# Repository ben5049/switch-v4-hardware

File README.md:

# Switch v4 Hardware

KiCad design files for the 4th iteration of my single pair Ethernet (SPE) switch. The firmware can be found in [unified-switch-firmware](https://github.com/ben5049/unified-switch-firmware).

Also see my post on [r/embedded](https://www.reddit.com/r/embedded/comments/1mxale6/i_built_a_single_pair_ethernet_switch/)!

## Design

See the [schematic](docs/schematics/switch-main-v4.pdf) for a block diagram and in-depth details.

The main switch chip is an [SJA1105QEL](https://www.nxp.com/products/SJA1105PQRS) from NXP. It is configured via SPI by an [STM32H573IIK3Q](https://www.st.com/resource/en/datasheet/stm32h573ai.pdf). The STM32 is also connected by reduced media independent interface (RMII) to the switch so it is able to send and receive management traffic such as Spanning Tree Protocol ([STP](https://en.wikipedia.org/wiki/Spanning_Tree_Protocol)) BPDUs as well as Precision Time Protocol (PTP) packets and diagnostic information.

The connections for each SJA1105 port are shown below:

| Port | Speed (Mbps) | Description                                            |
| ---- | ------------ | ------------------------------------------------------ |
| 0    | 100/1000     | Marvell 88Q2112 100/1000BASE-T1 Ethernet PHY           |
| 1    | 100/1000     | Marvell 88Q2112 100/1000BASE-T1 Ethernet PHY with PoDL |
| 2    | 100/1000     | Marvell 88Q2112 100/1000BASE-T1 Ethernet PHY with PoDL |
| 3    | 10           | Microchip LAN8671 10BASE-T1S Ethernet PHY with PoDL    |
| 4    | 100          | Internal STM32 management processor                    |

### PoDL PSE

Power over Datalines ([PoDL](https://en.wikipedia.org/wiki/Power_over_Ethernet#PoDL)) is similar to Power over Ethernet ([PoE](https://en.wikipedia.org/wiki/Power_over_Ethernet)) but for SPE. In regular PoE power is sent over the center taps of the transformers, however in SPE there is only one (or no) transformer so this wouldn't work. Instead, DC power is injected into the datalines in the Coupling Decoupling Network (CDN) using differential mode inductors (DMI). The switch is only capable of being a Power Sourcing Equipment (PSE) which powers other devices. It must get its own power through the other connectors on the board.

PoDL has been implemented on ports 1, 2 and 3 of the switch.

- Ports 1 and 2 are able to output 1.1A each and use a simple detection method before supplying power to a load. Firstly ~14mA is sent down the cable, then if the bus voltage is between 4.05 and 4.55V then the full supply is enabled (typically 24V). This is usually done by a zener diode on the other end of the cable.

- Port 3 is also able to output 1.1A and uses a custom multidrop PoDL implementation. Detection is done by powering the bus at 6.5V, then each device on the bus draws 1mA for every 1W of power they want. Then the full supply is enabled.

An [STM32H503KBU6](https://www.st.com/resource/en/datasheet/stm32h503eb.pdf) is used as a secondary processor to control the PoDL operations. It talks to the primary processor via UART through an optocoupler. This means the data and power circuits are galvanically isolated.

## Test Rig

The [test rig PCB](pcbs/switch-main-v4-test-rig) is designed so that its pogo pins align directly with the test pads on the bottom of the main switch board. This means a debugger can be connected without needing to include a header on the main board.

## Versions

| Version | Description |
| ------- | ----------- |
| v4.1.1  | Updated to Kicad v10 |
| v4.1.0  | Fixed bugs from first revision |
| v4.0.0  | First release |

See the [errata](docs/errata.md) for details on bugs.

## References

Datasheets:
- [88Q2112 Datasheet](https://www.infineon.com/assets/row/public/documents/10/49/infineon-brightlane-88q2110-88q2112-datasheet-datasheet-en.pdf) (requires an Infineon account)
- [SJA1105 Datasheet](https://www.nxp.com/docs/en/data-sheet/SJA1105PQRS.pdf)
- [LAN8671 Datasheet](https://ww1.microchip.com/downloads/aemDocuments/documents/AIS/ProductDocuments/DataSheets/LAN8670-1-2-Data-Sheet-60001573.pdf)

PoDL:
- [How to Implement an IEEE 802.3cg or 802.3bu-Compliant PoDL PSE](https://www.ti.com/lit/ab/snla395/snla395.pdf?ts=1745823061950) - TI
- [1000BASE-T1 PoDL Reference design](https://www.ti.com/lit/ug/tiduf49/tiduf49.pdf?ts=1746159399261&ref_url=https%253A%252F%252Fwww.google.com%252F) - TI
- [PSE Schematic](https://www.ti.com/lit/df/tidmco4/tidmco4.pdf?ts=1746307249429) - TI
- [IEEE 802.3cg 10BASE-T1L Power over Data Lines Powered Device Design](https://www.ti.com/lit/an/snvaa25a/snvaa25a.pdf?ts=1745871367852) - TI
    - References non-existent inductors :/
- [SINGLE PAIR ETHERNET FILTER DESIGN](https://www.we-online.com/files/pdf1/single_pair_ethernet.pdf) - WE
- [Power Injection Inductors for 10BASE-T1 PoDL](https://www.coilcraft.com/en-us/applications/power-injection-inductors-for-10base-t1-podl/) - Coilcraft
- [10BASE-T1L Converter w/ PoE+PoDL](https://matthewtran.dev/2024/08/10base-t1l-converter/)

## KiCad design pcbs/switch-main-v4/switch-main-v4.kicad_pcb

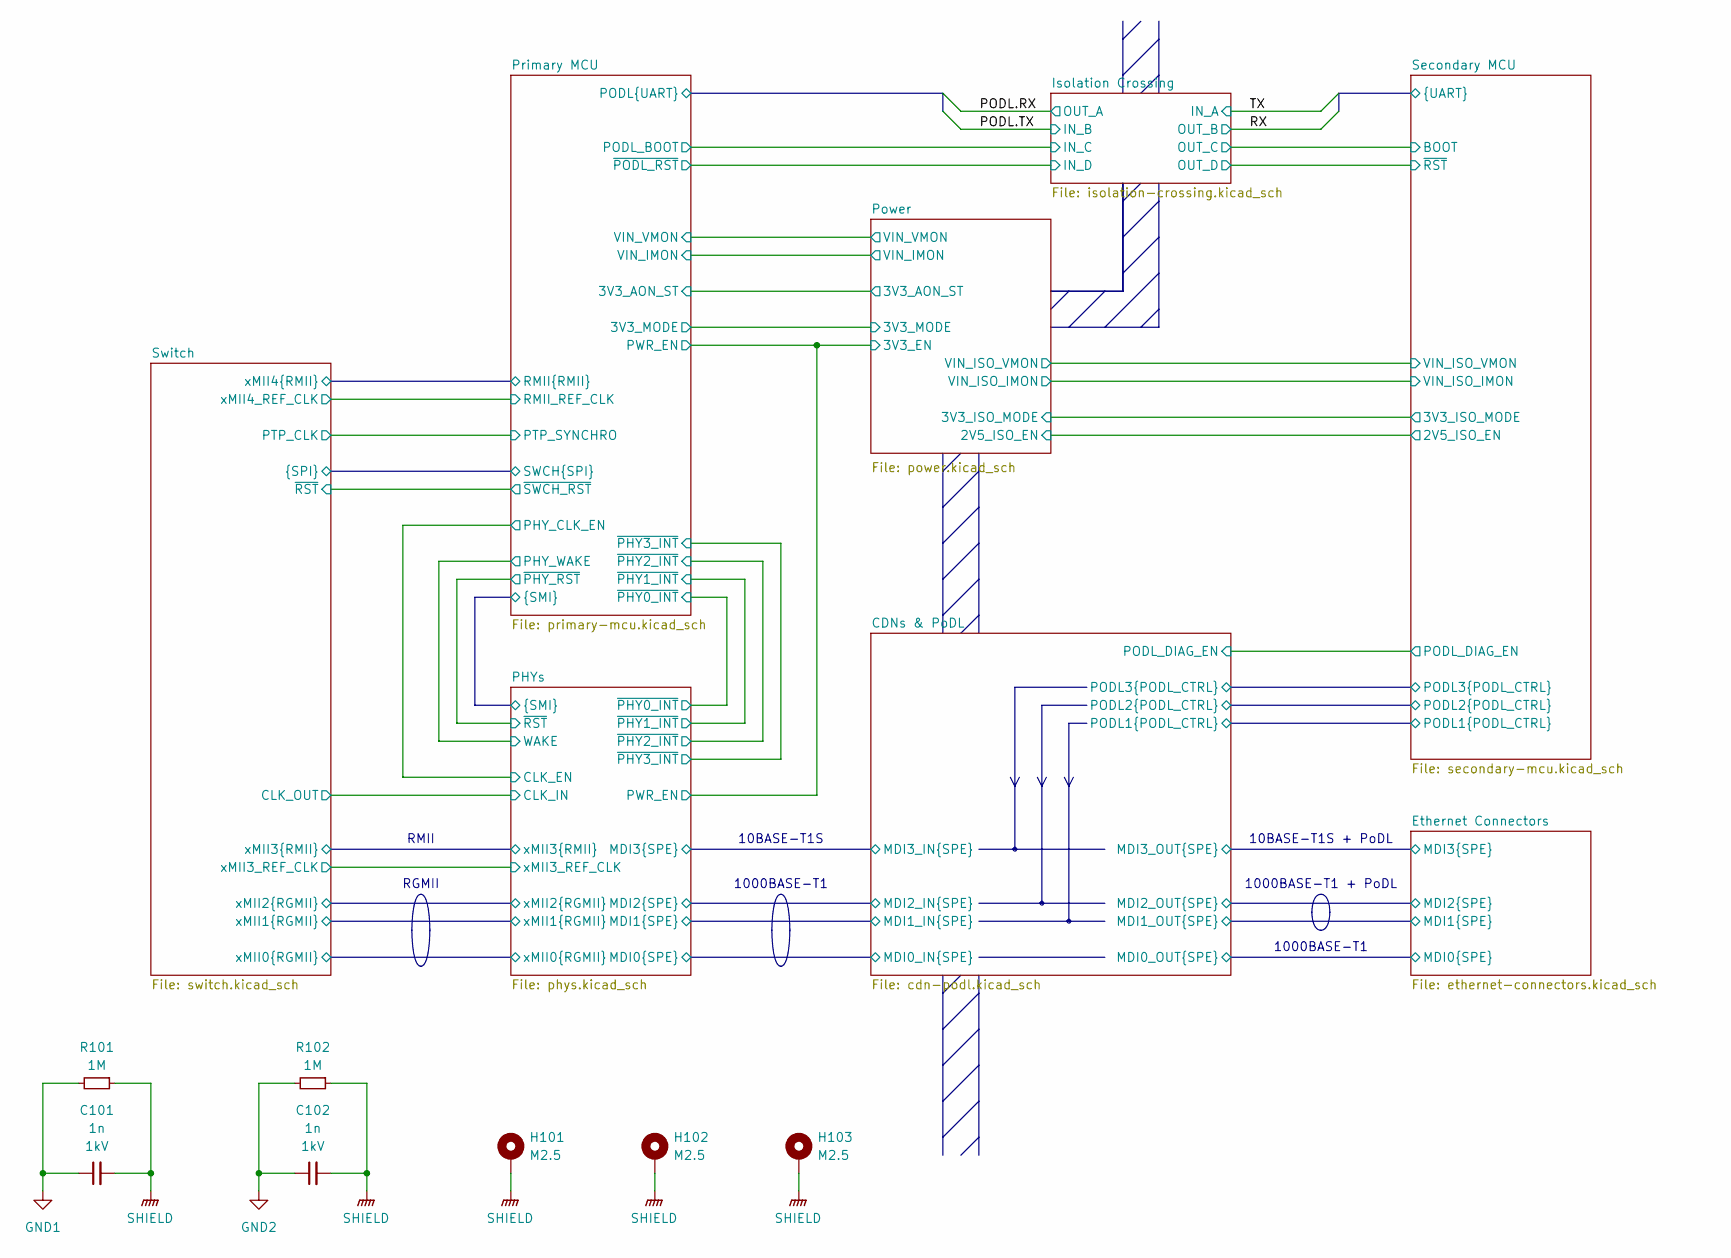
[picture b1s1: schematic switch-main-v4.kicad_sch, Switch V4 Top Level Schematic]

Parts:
C101, C102: 1n; C_0805; Voltage 1kV
H101, H102, H103: M2.5; MountingHole_2.7mm_M2.5_Pad
R101, R102: 1M; R_0805

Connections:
GND1: C101.1, R101.2; also elsewhere on the board
GND2: C102.1, R102.2; also elsewhere on the board
SHIELD: C101.2, C102.2, H101.1 (1_1), H102.1 (1_1), H103.1 (1_1), R101.1, R102.1; also elsewhere on the board

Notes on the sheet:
RGMII
RMII
10BASE-T1S
1000BASE-T1
1000BASE-T1 + PoDL
10BASE-T1S + PoDL

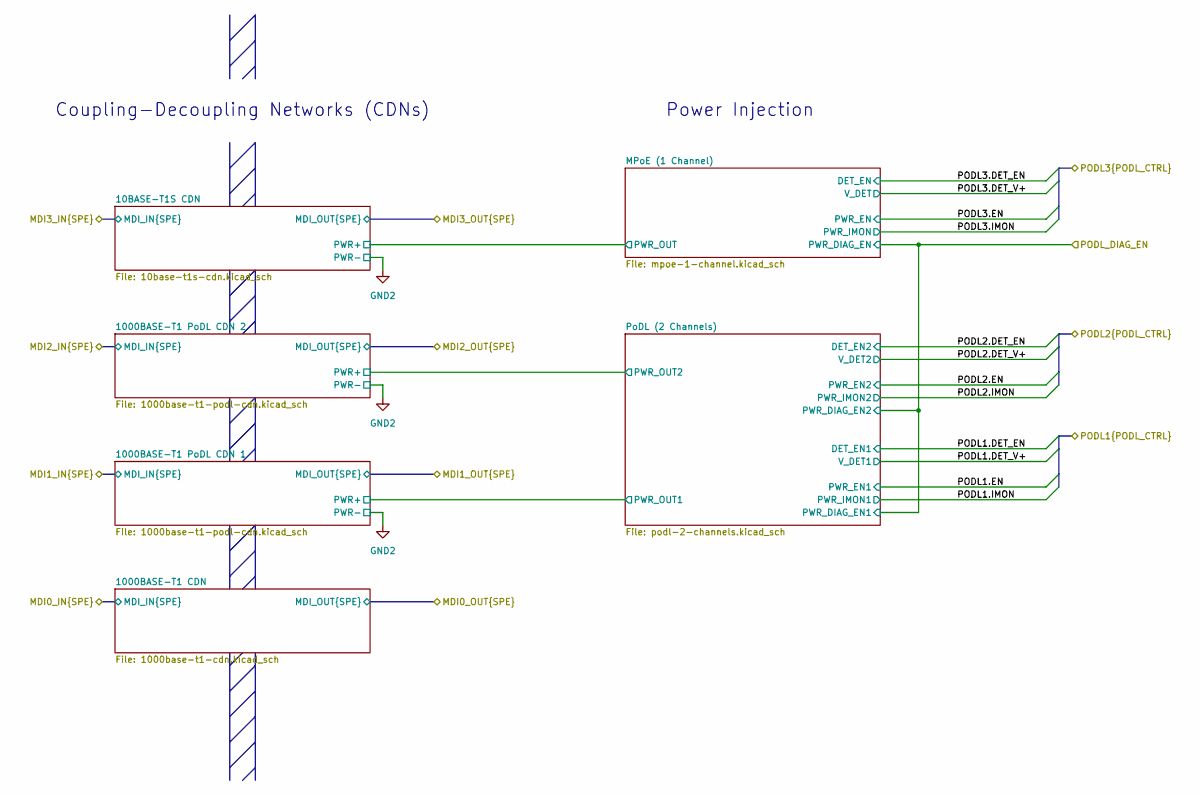
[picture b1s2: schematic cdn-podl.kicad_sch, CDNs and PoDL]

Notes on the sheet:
Power Injection
Coupling-Decoupling Networks (CDNs)

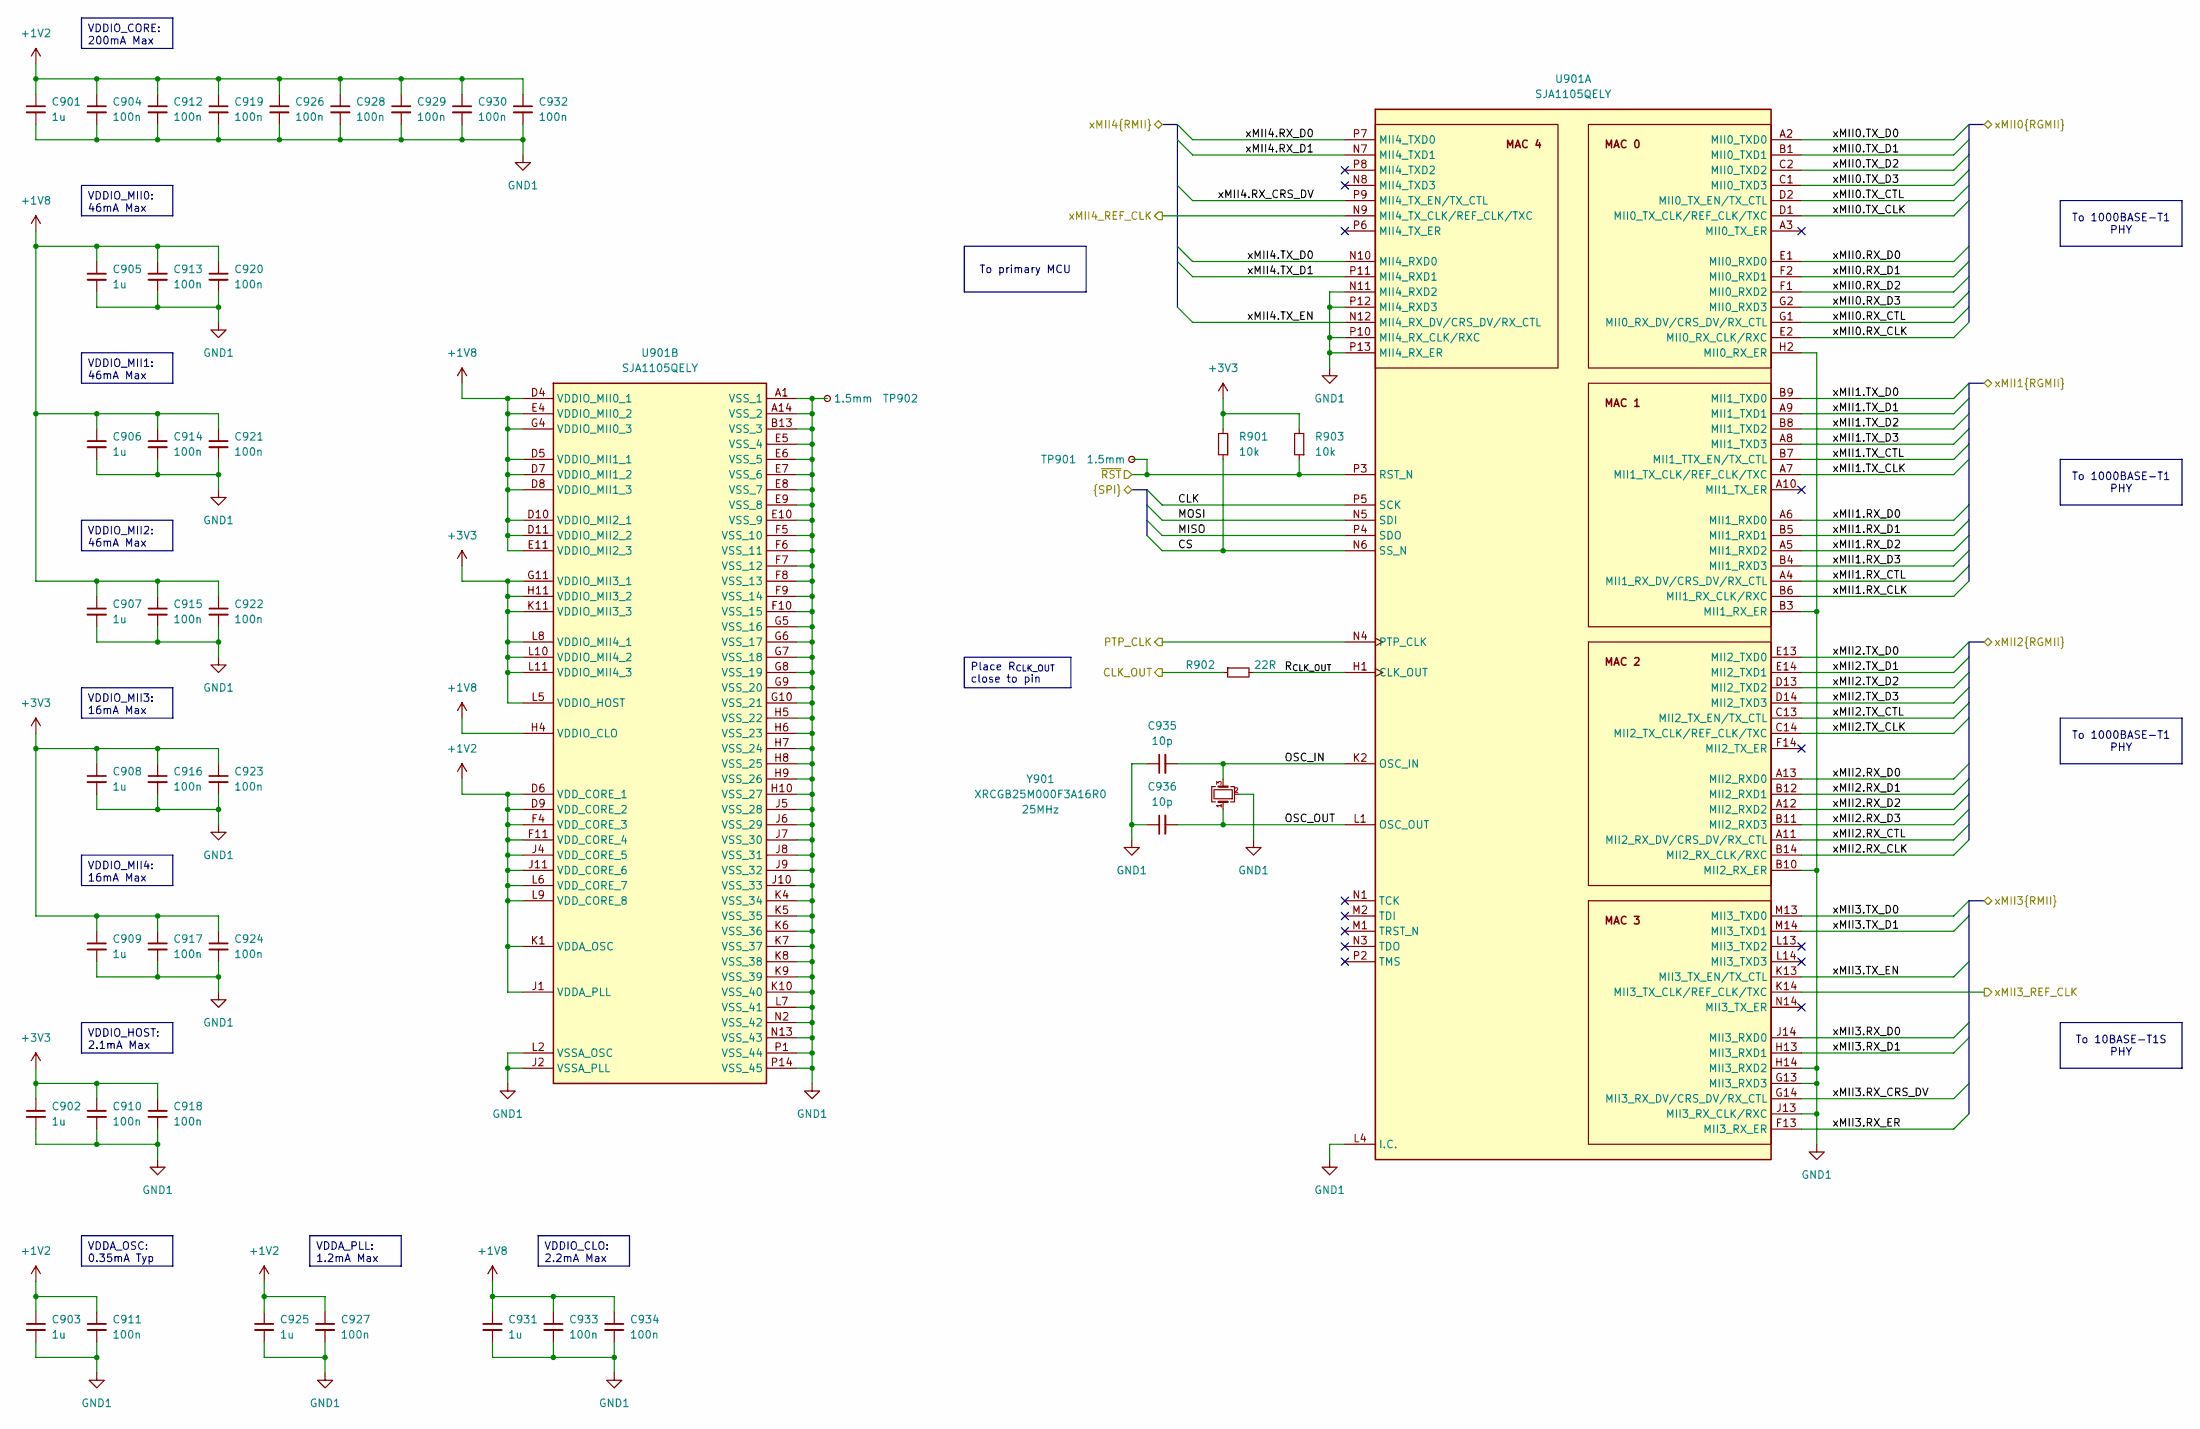
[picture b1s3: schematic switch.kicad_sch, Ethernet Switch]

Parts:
C901, C902, C903, C905, C906, C907, C908, C909, C925, C931: 1u; C_0402
C904, C910, C911, C912, C913, C914, C915, C916, C917, C918, C919, C920, C921, C922, C923, C924, C926, C927, C928, C929, C930, C932, C933, C934: 100n; C_0402
C935, C936: 10p; C_0402
R901, R903: 10k; R_0402
R902: 22R; R_0402
TP901, TP902: 1.5mm; TestPoint_Pad_D1.5mm
U901: SJA1105QELY; BGA159C80P14X14_1200X1200X150; Mouser Part Number 771-SJA1105QELY
Y901: XRCGB25M000F3A16R0

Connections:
+1V2: C901.1, C903.1, C904.1, C911.1, C912.1, C919.1, C925.1, C926.1, C927.1, C928.1, C929.1, C930.1, C932.1, U901.D6 (VDD_CORE_1), U901.D9 (VDD_CORE_2), U901.F4 (VDD_CORE_3), U901.F11 (VDD_CORE_4), U901.J1 (VDDA_PLL), U901.J4 (VDD_CORE_5), U901.J11 (VDD_CORE_6), U901.K1 (VDDA_OSC), U901.L6 (VDD_CORE_7), U901.L9 (VDD_CORE_8); also elsewhere on the board
+1V8: C905.1, C906.1, C907.1, C913.1, C914.1, C915.1, C920.1, C921.1, C922.1, C931.1, C933.1, C934.1, U901.D4 (VDDIO_MII0_1), U901.D5 (VDDIO_MII1_1), U901.D7 (VDDIO_MII1_2), U901.D8 (VDDIO_MII1_3), U901.D10 (VDDIO_MII2_1), U901.D11 (VDDIO_MII2_2), U901.E4 (VDDIO_MII0_2), U901.E11 (VDDIO_MII2_3), U901.G4 (VDDIO_MII0_3), U901.H4 (VDDIO_CLO); also elsewhere on the board
+3V3: C902.1, C908.1, C909.1, C910.1, C916.1, C917.1, C918.1, C923.1, C924.1, R901.2, R903.2, U901.G11 (VDDIO_MII3_1), U901.H11 (VDDIO_MII3_2), U901.K11 (VDDIO_MII3_3), U901.L5 (VDDIO_HOST), U901.L8 (VDDIO_MII4_1), U901.L10 (VDDIO_MII4_2), U901.L11 (VDDIO_MII4_3); also elsewhere on the board
/PHYs/CLK_IN: R902.1; also elsewhere on the board
/PHYs/xMII0.RX_CLK: U901.E2 (MII0_RX_CLK/RXC); also elsewhere on the board
/PHYs/xMII0.RX_CTL: U901.G1 (MII0_RX_DV/CRS_DV/RX_CTL); also elsewhere on the board
/PHYs/xMII0.RX_D0: U901.E1 (MII0_RXD0); also elsewhere on the board
/PHYs/xMII0.RX_D1: U901.F2 (MII0_RXD1); also elsewhere on the board
/PHYs/xMII0.RX_D2: U901.F1 (MII0_RXD2); also elsewhere on the board
/PHYs/xMII0.RX_D3: U901.G2 (MII0_RXD3); also elsewhere on the board
/PHYs/xMII0.TX_CLK: U901.D1 (MII0_TX_CLK/REF_CLK/TXC); also elsewhere on the board
/PHYs/xMII0.TX_CTL: U901.D2 (MII0_TX_EN/TX_CTL); also elsewhere on the board
/PHYs/xMII0.TX_D0: U901.A2 (MII0_TXD0); also elsewhere on the board
/PHYs/xMII0.TX_D1: U901.B1 (MII0_TXD1); also elsewhere on the board
/PHYs/xMII0.TX_D2: U901.C2 (MII0_TXD2); also elsewhere on the board
/PHYs/xMII0.TX_D3: U901.C1 (MII0_TXD3); also elsewhere on the board
/PHYs/xMII1.RX_CLK: U901.B6 (MII1_RX_CLK/RXC); also elsewhere on the board
/PHYs/xMII1.RX_CTL: U901.A4 (MII1_RX_DV/CRS_DV/RX_CTL); also elsewhere on the board
/PHYs/xMII1.RX_D0: U901.A6 (MII1_RXD0); also elsewhere on the board
/PHYs/xMII1.RX_D1: U901.B5 (MII1_RXD1); also elsewhere on the board
/PHYs/xMII1.RX_D2: U901.A5 (MII1_RXD2); also elsewhere on the board
/PHYs/xMII1.RX_D3: U901.B4 (MII1_RXD3); also elsewhere on the board
/PHYs/xMII1.TX_CLK: U901.A7 (MII1_TX_CLK/REF_CLK/TXC); also elsewhere on the board
/PHYs/xMII1.TX_CTL: U901.B7 (MII1_TTX_EN/TX_CTL); also elsewhere on the board
/PHYs/xMII1.TX_D0: U901.B9 (MII1_TXD0); also elsewhere on the board
/PHYs/xMII1.TX_D1: U901.A9 (MII1_TXD1); also elsewhere on the board
/PHYs/xMII1.TX_D2: U901.B8 (MII1_TXD2); also elsewhere on the board
/PHYs/xMII1.TX_D3: U901.A8 (MII1_TXD3); also elsewhere on the board
/PHYs/xMII2.RX_CLK: U901.B14 (MII2_RX_CLK/RXC); also elsewhere on the board
/PHYs/xMII2.RX_CTL: U901.A11 (MII2_RX_DV/CRS_DV/RX_CTL); also elsewhere on the board
/PHYs/xMII2.RX_D0: U901.A13 (MII2_RXD0); also elsewhere on the board
/PHYs/xMII2.RX_D1: U901.B12 (MII2_RXD1); also elsewhere on the board
/PHYs/xMII2.RX_D2: U901.A12 (MII2_RXD2); also elsewhere on the board
/PHYs/xMII2.RX_D3: U901.B11 (MII2_RXD3); also elsewhere on the board
/PHYs/xMII2.TX_CLK: U901.C14 (MII2_TX_CLK/REF_CLK/TXC); also elsewhere on the board
/PHYs/xMII2.TX_CTL: U901.C13 (MII2_TX_EN/TX_CTL); also elsewhere on the board
/PHYs/xMII2.TX_D0: U901.E13 (MII2_TXD0); also elsewhere on the board
/PHYs/xMII2.TX_D1: U901.E14 (MII2_TXD1); also elsewhere on the board
/PHYs/xMII2.TX_D2: U901.D13 (MII2_TXD2); also elsewhere on the board
/PHYs/xMII2.TX_D3: U901.D14 (MII2_TXD3); also elsewhere on the board
/PHYs/xMII3.RX_CRS_DV: U901.G14 (MII3_RX_DV/CRS_DV/RX_CTL); also elsewhere on the board
/PHYs/xMII3.RX_D0: U901.J14 (MII3_RXD0); also elsewhere on the board
/PHYs/xMII3.RX_D1: U901.H13 (MII3_RXD1); also elsewhere on the board
/PHYs/xMII3.RX_ER: U901.F13 (MII3_RX_ER); also elsewhere on the board
/PHYs/xMII3.TX_D0: U901.M13 (MII3_TXD0); also elsewhere on the board
/PHYs/xMII3.TX_D1: U901.M14 (MII3_TXD1); also elsewhere on the board
/PHYs/xMII3.TX_EN: U901.K13 (MII3_TX_EN/TX_CTL); also elsewhere on the board
/PHYs/xMII3_REF_CLK: U901.K14 (MII3_TX_CLK/REF_CLK/TXC); also elsewhere on the board
/Primary MCU/PTP_SYNCHRO: U901.N4 (PTP_CLK); also elsewhere on the board
/Primary MCU/RMII.RX_CRS_DV: U901.P9 (MII4_TX_EN/TX_CTL); also elsewhere on the board
/Primary MCU/RMII.RX_D0: U901.P7 (MII4_TXD0); also elsewhere on the board
/Primary MCU/RMII.RX_D1: U901.N7 (MII4_TXD1); also elsewhere on the board
/Primary MCU/RMII.TX_D0: U901.N10 (MII4_RXD0); also elsewhere on the board
/Primary MCU/RMII.TX_D1: U901.P11 (MII4_RXD1); also elsewhere on the board
/Primary MCU/RMII.TX_EN: U901.N12 (MII4_RX_DV/CRS_DV/RX_CTL); also elsewhere on the board
/Primary MCU/RMII_REF_CLK: U901.N9 (MII4_TX_CLK/REF_CLK/TXC); also elsewhere on the board
/Primary MCU/SWCH.CLK: U901.P5 (SCK); also elsewhere on the board
/Primary MCU/SWCH.CS: R901.1, U901.N6 (SS_N); also elsewhere on the board
/Primary MCU/SWCH.MISO: U901.P4 (SDO); also elsewhere on the board
/Primary MCU/SWCH.MOSI: U901.N5 (SDI); also elsewhere on the board
/Primary MCU/~SWCH_RST: R903.1, TP901.1 (1_1), U901.P3 (RST_N); also elsewhere on the board
/Switch/OSC_IN: C935.2, U901.K2 (OSC_IN), Y901.3
/Switch/OSC_OUT: C936.2, U901.L1 (OSC_OUT), Y901.1
/Switch/R_{CLK_OUT}: R902.2, U901.H1 (CLK_OUT)
GND1: C901.2, C902.2, C903.2, C904.2, C905.2, C906.2, C907.2, C908.2, C909.2, C910.2, C911.2, C912.2, C913.2, C914.2, C915.2, C916.2, C917.2, C918.2, C919.2, C920.2, C921.2, C922.2, C923.2, C924.2, C925.2, C926.2, C927.2, C928.2, C929.2, C930.2, C931.2, C932.2, C933.2, C934.2, C935.1, C936.1, TP902.1 (1_1), U901.A1 (VSS_1), U901.A14 (VSS_2), U901.B3 (MII1_RX_ER), U901.B10 (MII2_RX_ER), U901.B13 (VSS_3), U901.E5 (VSS_4), U901.E6 (VSS_5), U901.E7 (VSS_6), U901.E8 (VSS_7), U901.E9 (VSS_8), U901.E10 (VSS_9), U901.F5 (VSS_10), U901.F6 (VSS_11), U901.F7 (VSS_12), U901.F8 (VSS_13), U901.F9 (VSS_14), U901.F10 (VSS_15), U901.G5 (VSS_16), U901.G6 (VSS_17), U901.G7 (VSS_18), U901.G8 (VSS_19), U901.G9 (VSS_20), U901.G10 (VSS_21), U901.G13 (MII3_RXD3), U901.H2 (MII0_RX_ER), U901.H5 (VSS_22), U901.H6 (VSS_23), U901.H7 (VSS_24), U901.H8 (VSS_25), U901.H9 (VSS_26), U901.H10 (VSS_27), U901.H14 (MII3_RXD2), U901.J2 (VSSA_PLL), U901.J5 (VSS_28), U901.J6 (VSS_29), U901.J7 (VSS_30), U901.J8 (VSS_31), U901.J9 (VSS_32), U901.J10 (VSS_33), U901.J13 (MII3_RX_CLK/RXC), U901.K4 (VSS_34), U901.K5 (VSS_35), U901.K6 (VSS_36), U901.K7 (VSS_37), U901.K8 (VSS_38), U901.K9 (VSS_39), U901.K10 (VSS_40), U901.L2 (VSSA_OSC), U901.L4 (I.C.), U901.L7 (VSS_41), U901.N2 (VSS_42), U901.N11 (MII4_RXD2), U901.N13 (VSS_43), U901.P1 (VSS_44), U901.P10 (MII4_RX_CLK/RXC), U901.P12 (MII4_RXD3), U901.P13 (MII4_RX_ER), U901.P14 (VSS_45), Y901.2 (G), Y901.4 (G); also elsewhere on the board

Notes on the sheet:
To 1000BASE-T1 PHY
VDDIO_MII3: 16mA Max
VDDIO_CLO: 2.2mA Max
VDDIO_MII2: 46mA Max
VDDIO_HOST: 2.1mA Max
VDDA_OSC: 0.35mA Typ
VDDIO_MII0: 46mA Max
To 10BASE-T1S PHY
VDDA_PLL: 1.2mA Max
VDDIO_CORE: 200mA Max
Place R_{CLK_OUT} close to pin
VDDIO_MII4: 16mA Max
To primary MCU
VDDIO_MII1: 46mA Max

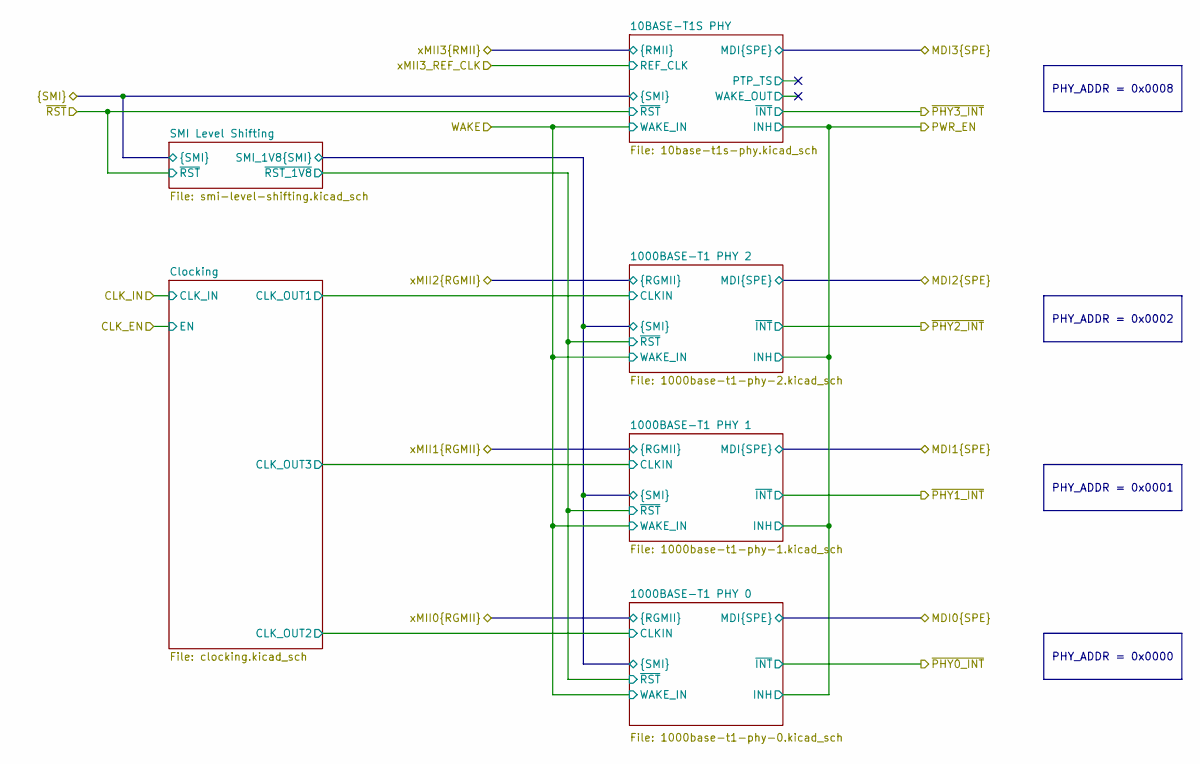
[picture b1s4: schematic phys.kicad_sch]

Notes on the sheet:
PHY_ADDR = 0x0000
PHY_ADDR = 0x0008
PHY_ADDR = 0x0001
PHY_ADDR = 0x0002

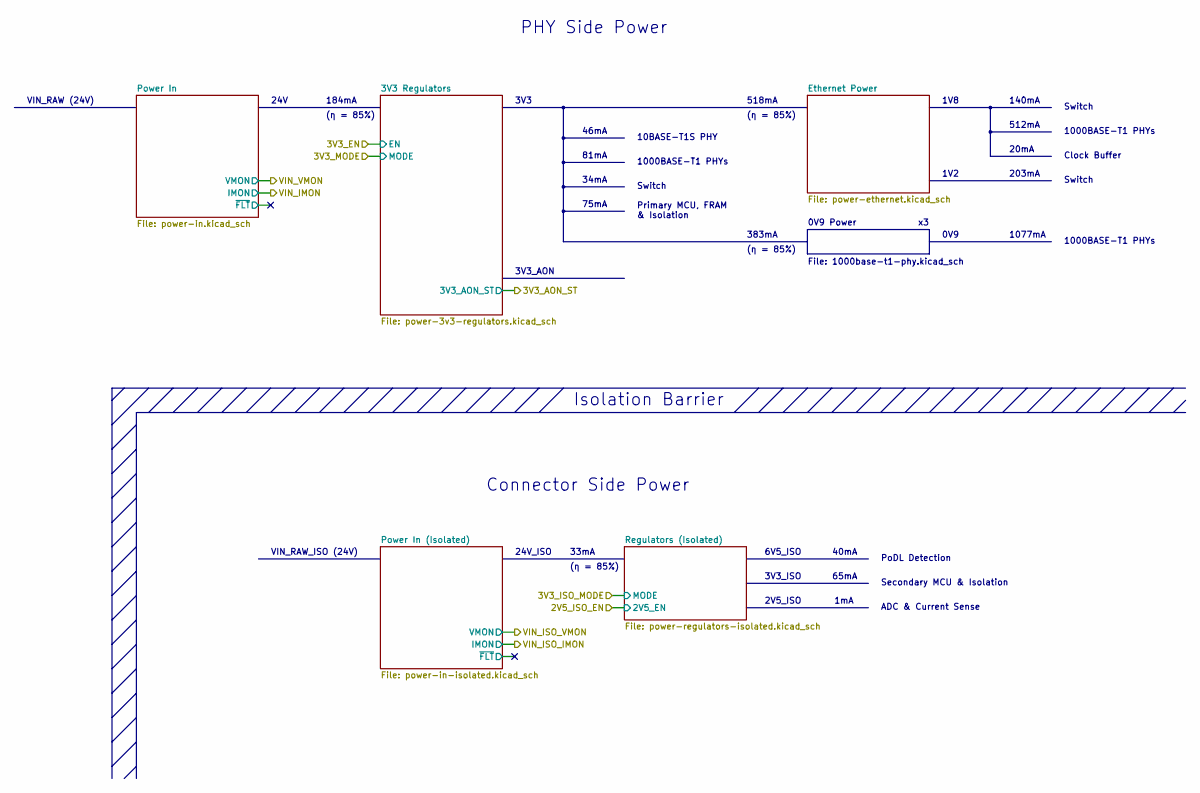
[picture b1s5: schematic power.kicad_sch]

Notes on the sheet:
1V2
Primary MCU, FRAM & Isolation
VIN_RAW_ISO (24V)
34mA
81mA
VIN_RAW (24V)
(η = 85%)
Clock Buffer
Switch
40mA
1V8
10BASE-T1S PHY
3V3
140mA
24V_ISO
33mA
512mA
1mA
46mA
0V9 Power
1000BASE-T1 PHYs
24V
File: 1000base-t1-phy.kicad_sch
518mA
PHY Side Power
184mA
1077mA
6V5_ISO
Isolation Barrier
PoDL Detection
2V5_ISO
Connector Side Power
383mA
203mA
75mA
Secondary MCU & Isolation
65mA
ADC & Current Sense
3V3_AON
20mA

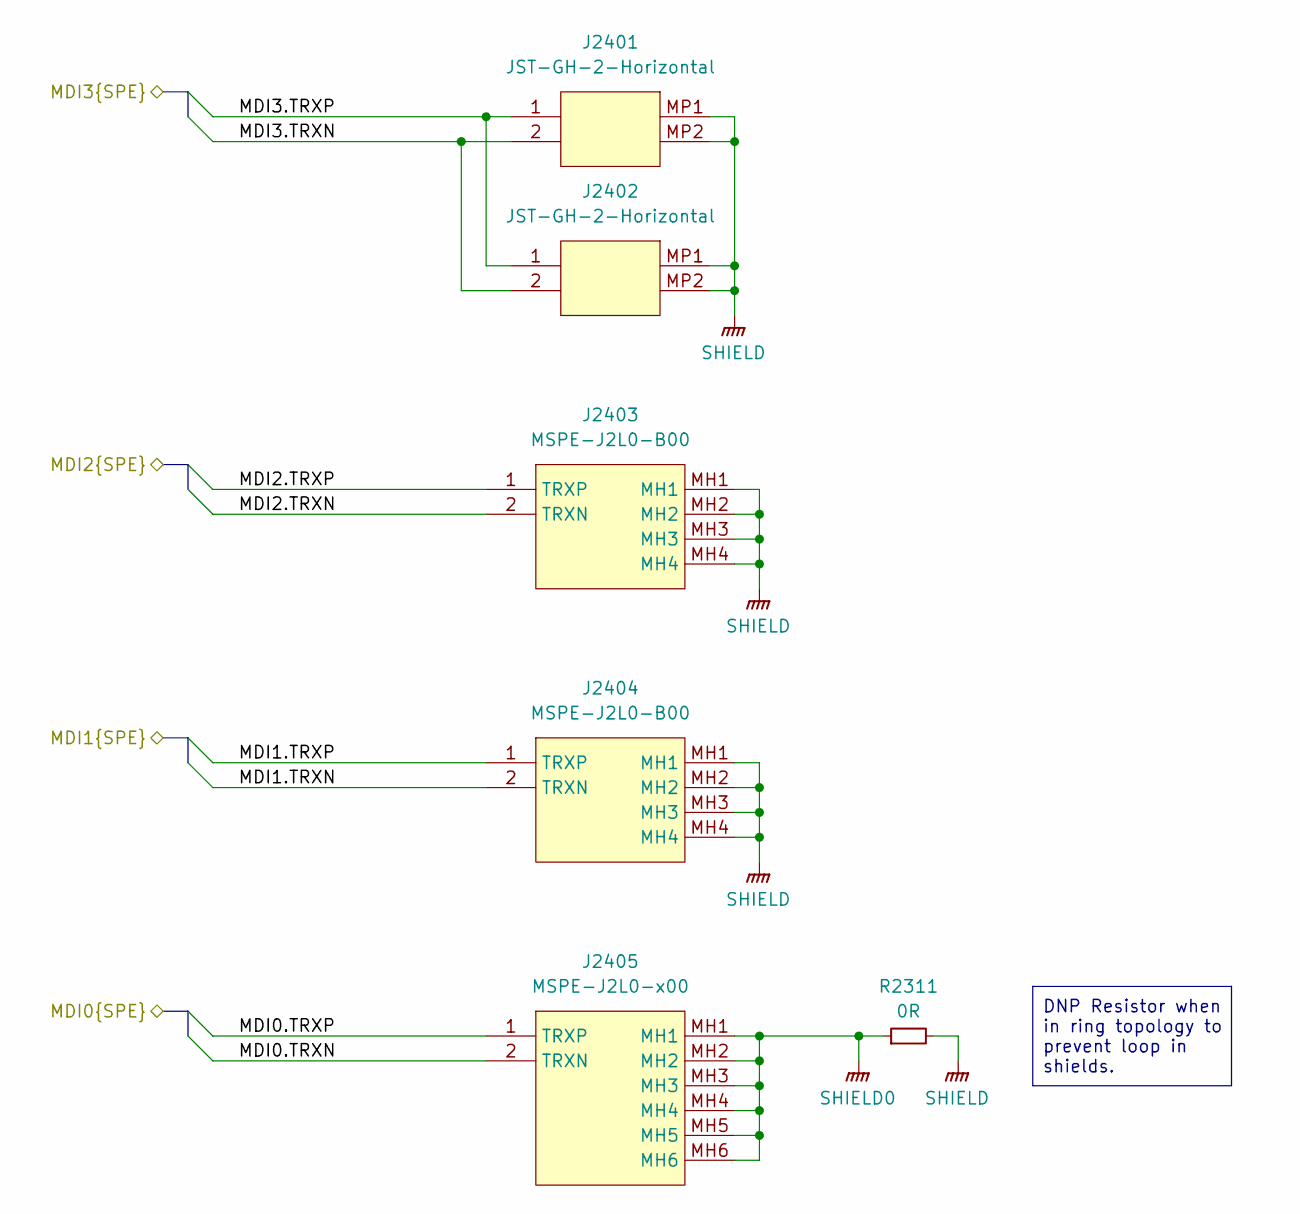
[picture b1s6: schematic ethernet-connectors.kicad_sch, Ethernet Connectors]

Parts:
J2401, J2402: JST-GH-2-Horizontal; JST_GH_SM02B-GHS-TB_1x02-1MP_P1.25mm_Horizontal
J2403, J2404: MSPE-J2L0-B00; MSPEJ2L0B00; Mouser Part Number 523-MSPE-J2L0-B00
J2405: MSPE-J2L0-x00; MSPEJ2L0x00; Mouser Part Number 523-MSPE-J2L0-B00
R2311: 0R; R_0402

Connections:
/CDNs & PoDL/MDI0_OUT.TRXN: J2405.2 (TRXN); also elsewhere on the board
/CDNs & PoDL/MDI0_OUT.TRXP: J2405.1 (TRXP); also elsewhere on the board
/CDNs & PoDL/MDI1_OUT.TRXN: J2404.2 (TRXN); also elsewhere on the board
/CDNs & PoDL/MDI1_OUT.TRXP: J2404.1 (TRXP); also elsewhere on the board
/CDNs & PoDL/MDI2_OUT.TRXN: J2403.2 (TRXN); also elsewhere on the board
/CDNs & PoDL/MDI2_OUT.TRXP: J2403.1 (TRXP); also elsewhere on the board
/CDNs & PoDL/MDI3_OUT.TRXN: J2401.2, J2402.2; also elsewhere on the board
/CDNs & PoDL/MDI3_OUT.TRXP: J2401.1, J2402.1; also elsewhere on the board
SHIELD: J2401.MP1, J2401.MP2, J2402.MP1, J2402.MP2, J2403.MH1, J2403.MH2, J2403.MH3, J2403.MH4, J2404.MH1, J2404.MH2, J2404.MH3, J2404.MH4, R2311.2; also elsewhere on the board
SHIELD0: J2405.MH1, J2405.MH2, J2405.MH3, J2405.MH4, J2405.MH5, J2405.MH6, R2311.1; also elsewhere on the board

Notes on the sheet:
DNP Resistor when in ring topology to prevent loop in shields.
